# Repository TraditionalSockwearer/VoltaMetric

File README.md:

# VoltaMetric (Project Blueprint)

**VoltaMetric** is an embedded engineering initiative to build a dual-channel, high-precision power analyser using the **.NET nanoFramework**.

This project aims to combine C# firmware and measurements of AC and DV simultaneously, logging telemetry to an onboard secure storage system.

---

## Project Goals

1.  **Dual-Rail Physics:** Implement simultaneous sampling of AC Mains (via CT Coil) and DC High Voltage (via Shunt).
2.  **Protocol Bridging:** Create a C# implementation of the **Modbus RTU** protocol over RS485 to interface with industrial sensors.
3.  **Safety Isolation:** Design a hardware layer that optically isolates the microcontroller logic (3.3V) from the measurement rails (240V/300V).
4.  **Autonomous Logging:** Implement a file management system to persist time-series energy data to SD Card storage in JSON format.

---

## Planned Architecture

### Hardware Stack
The system is built around the **Seeed Studio XIAO RP2040**, chosen for its dual-core Cortex M0+ processor and native support for .NET.

* **MCU:** Seeed XIAO RP2040 (C# / .NET nanoFramework)
* **AC Sensor:** PZEM-004T V3.0 (UART / Optical Isolation)
* **DC Sensor:** PZEM-017 (RS485 Modbus)
* **HMI:** 0.96" OLED Display (I2C)

### Logic Flow Diagram
The system uses a "Split-Stack" design to separate high-voltage physics from low-voltage logic.

```mermaid
graph TD
    A[AC Mains 240V] -.->|Isolation| B(AC Sensor)
    C[DC Source 300V] -.->|Shunt| D(DC Sensor)
    
    B -->|UART| E{Level Shifter}
    D -->|RS485| F[MAX485 Adapter]
    F -->|UART| E
    
    E -->|3.3V Logic| G[XIAO RP2040 Controller]
    
    G -->|I2C| H[OLED Dashboard]
    G -->|SPI| I[SD Persistence Layer]
```
## Safety Warning
### DANGER: High Voltage Project

This device interfaces directly with Mains Voltage (**110V**/**240V** AC) and High Voltage DC (>**60V**).

* **Risk of Electrocution**: Never touch the sensor modules or PCB while mains power is connected.

* **Enclosure**: The device must be mounted inside a non-conductive ABS plastic enclosure before use.

* **Isolation**: Ensure the Logic Level Shifter is correctly installed to maintain optical isolation between the High Voltage side and the USB/Logic side.

The author assumes no liability for injuries or damage caused by the assembly or use of this device.

## License
This project is licensed under the **MIT License** - see the **LICENSE** file for details.

Built with ❤️ and **C#** by **Arjun**

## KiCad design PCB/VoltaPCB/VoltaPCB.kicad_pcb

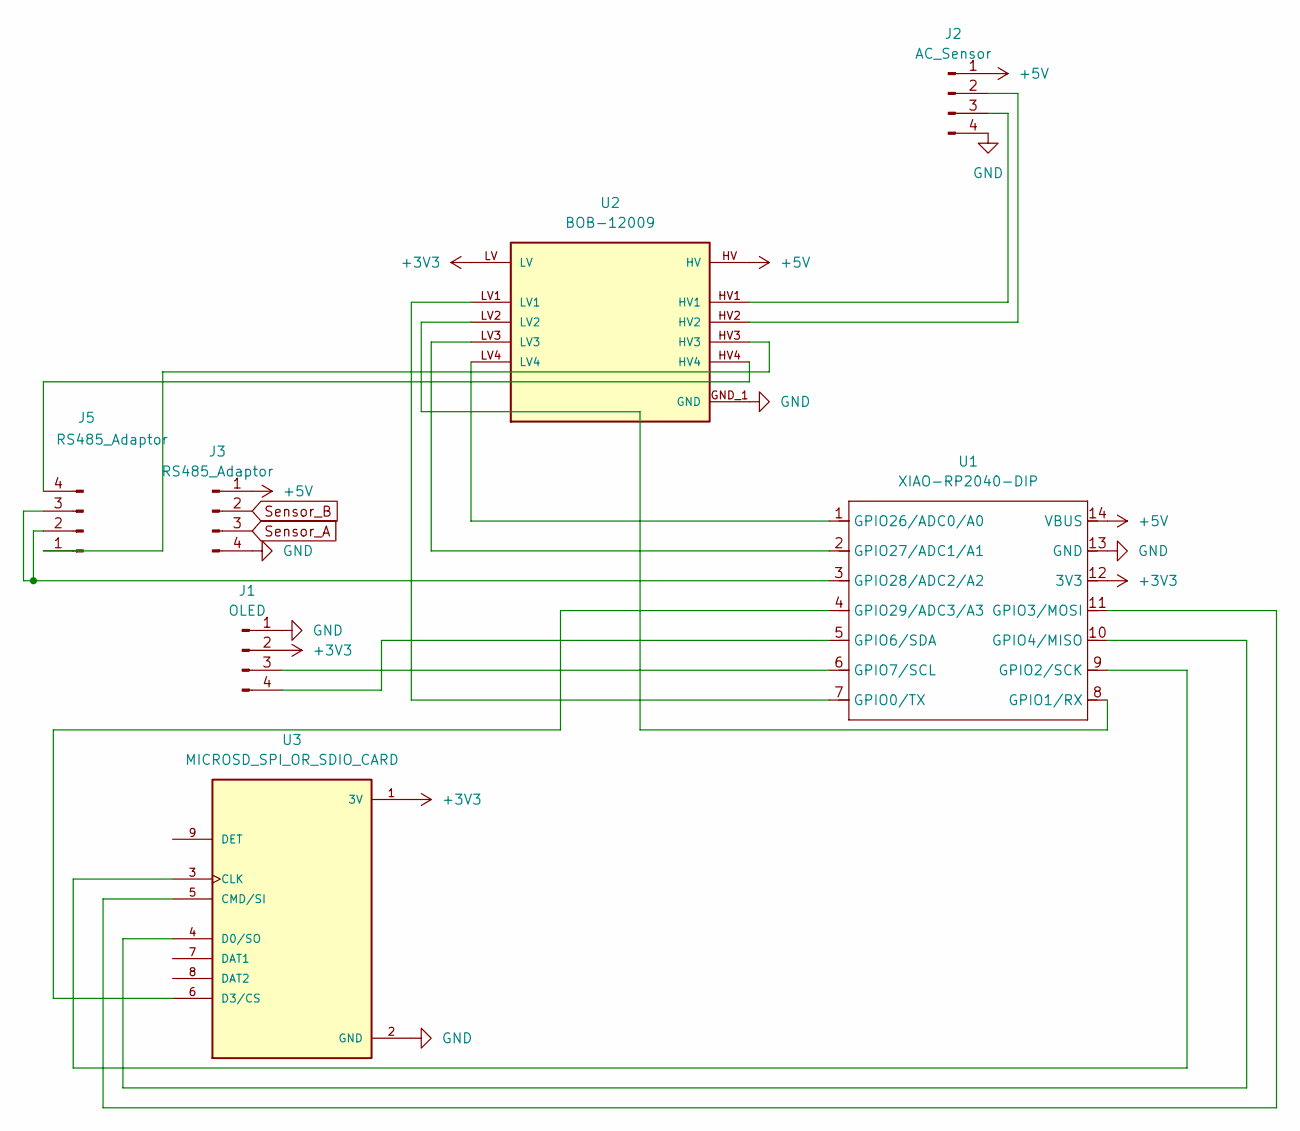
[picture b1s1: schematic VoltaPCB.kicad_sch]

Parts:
J1: OLED; SSD1306-0.91-OLED-4pin-128x32
J2: AC_Sensor; PinHeader_1x04_P2.54mm_Vertical
J3, J5: RS485_Adaptor; PinHeader_1x04_P2.54mm_Vertical
U1: XIAO-RP2040-DIP
U2: BOB-12009; CONV_BOB-12009; PARTREV 01
U3: MICROSD_SPI_OR_SDIO_CARD; MODULE_MICROSD_SPI_OR_SDIO_CARD; PARTREV B

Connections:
+3V3: J1.2, U1.12 (3V3), U2.LV, U3.1 (3V)
+5V: J2.1, J3.1, U1.14 (VBUS), U2.HV
GND: J1.1, J2.4, J3.4, U1.13 (GND), U2.GND_1 (GND), U2.GND_2 (GND), U3.2 (GND)
unnamed: J1.3, U1.6 (GPIO7/SCL)
unnamed: J1.4, U1.5 (GPIO6/SDA)
unnamed: J2.2, U2.HV2
unnamed: J2.3, U2.HV1
unnamed: J5.1, U2.HV3
unnamed: J5.2, J5.3, U1.3 (GPIO28/ADC2/A2)
unnamed: J5.4, U2.HV4
unnamed: U1.7 (GPIO0/TX), U2.LV1
unnamed: U1.8 (GPIO1/RX), U2.LV2
unnamed: U1.9 (GPIO2/SCK), U3.3 (CLK)
unnamed: U1.11 (GPIO3/MOSI), U3.5 (CMD/SI)
unnamed: U1.10 (GPIO4/MISO), U3.4 (D0/SO)
unnamed: U1.1 (GPIO26/ADC0/A0), U2.LV4
unnamed: U1.2 (GPIO27/ADC1/A1), U2.LV3
unnamed: U1.4 (GPIO29/ADC3/A3), U3.6 (D3/CS)
Sensor_A: J3.3
Sensor_B: J3.2

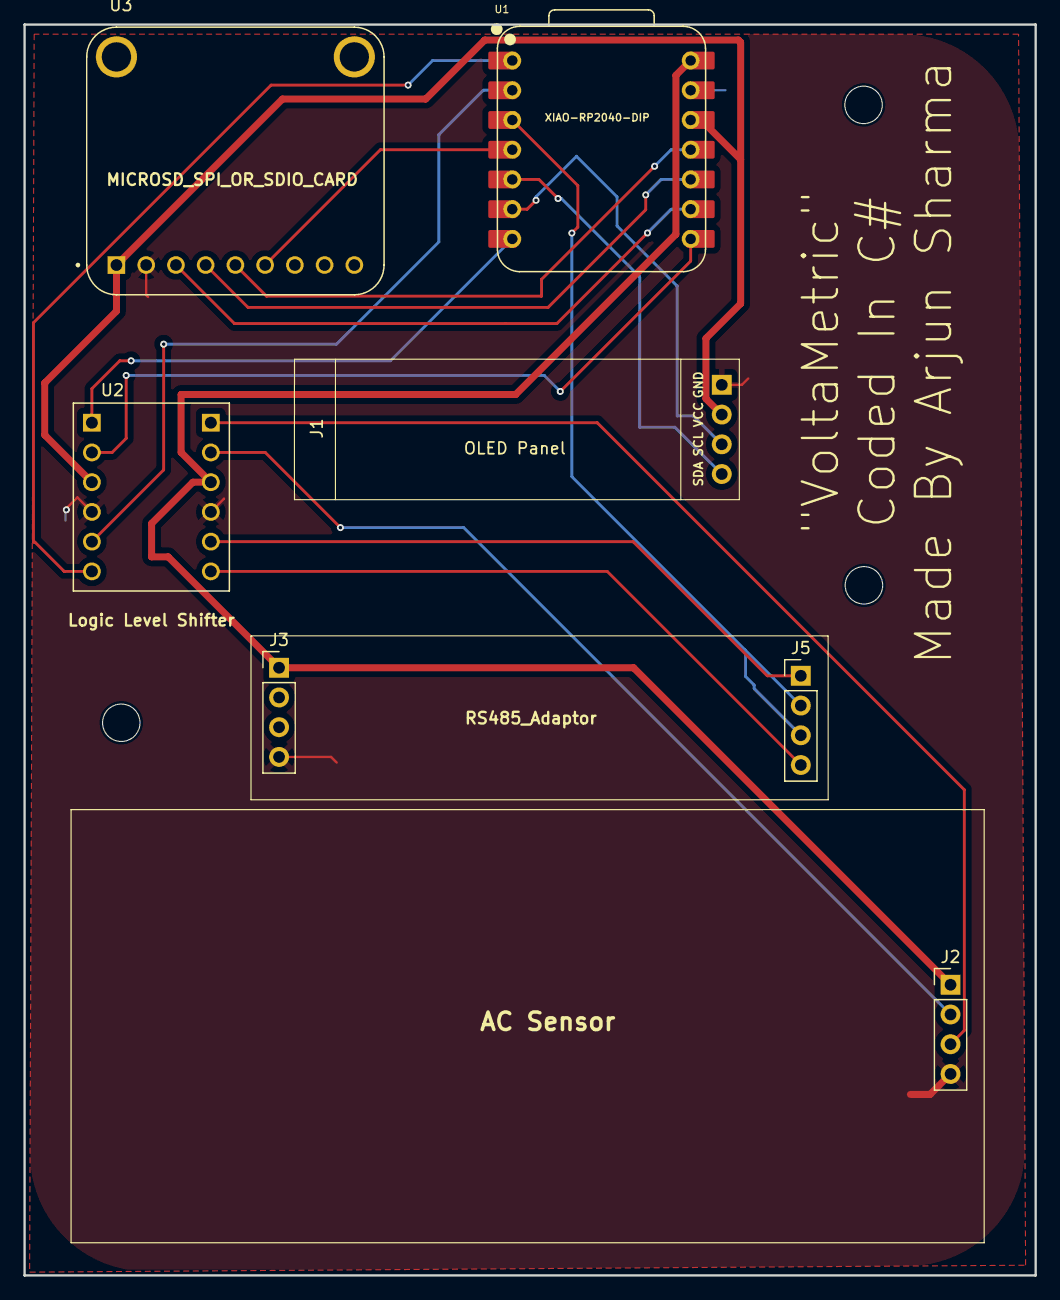
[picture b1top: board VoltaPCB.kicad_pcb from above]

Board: 2 copper layers, 86.4 x 106.9 mm, 7 parts (0 on the bottom side), 18 nets.

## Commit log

2025-12-16 Addition Of all Library and first revision of PCB and Schematic
